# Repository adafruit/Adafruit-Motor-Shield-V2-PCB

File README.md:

## Adafruit Motor Shield V2 PCB

<a href="http://www.adafruit.com/products/1438"><br/>
Click here to purchase one from the Adafruit shop</a>

PCB files for Adafruit Motor Shield V2. 
- http://www.adafruit.com/products/1438

### DESCRIPTION
The original Adafruit Motorshield kit is one of our most beloved kits, which is why we decided to make something even better. We have upgraded the shield kit to make the bestest, easiest way to drive DC and Stepper motors. This shield will make quick work of your next robotics project! We kept the ability to drive up to 4 DC motors or 2 stepper motors, but added many improvements:

Instead of a L293D darlington driver, we now have the TB6612 MOSFET drivers with 1.2A per channel current capability (you can draw up to 3A peak for approx 20ms at a time). It also has much lower voltage drops across the motor so you get more torque out of your batteries, and there are built-in flyback diodes as well.

Instead of using a latch and the Arduino's PWM pins, we have a fully-dedicated PWM driver chip onboard. This chip handles all the motor and speed controls over I2C. Only two data pins (SDA & SCL in addition to the power pins GND & 5V) are required to drive the multiple motors, and since it's I2C you can also connect any other I2C devices or shields to the same pins. This also makes it drop-in compatible with any Arduino, such as the Uno, Due, Leonardo and Mega R3.

Completely stackable design: 5 address-select pins means up to 32 stackable shields: that's 64 steppers or 128 DC motors! What on earth could you do with that many steppers? I have no idea but if you come up with something send us a photo because that would be a pretty glorious project.

Lots of other little improvements such as a polarity protection FET on the power pins and a bit of prototyping area. And the shield is assembled and tested here at Adafruit so all you have to do is solder on straight or stacking headers and the terminal blocks.

### License

Adafruit invests time and resources providing this open source design, please support Adafruit and open-source hardware by purchasing products from [Adafruit.com](https://www.adafruit.com)!

Creative Commons Attribution, Share-Alike license, check license.txt for more information All text above must be included in any redistribution - 
See license.txt for more information.

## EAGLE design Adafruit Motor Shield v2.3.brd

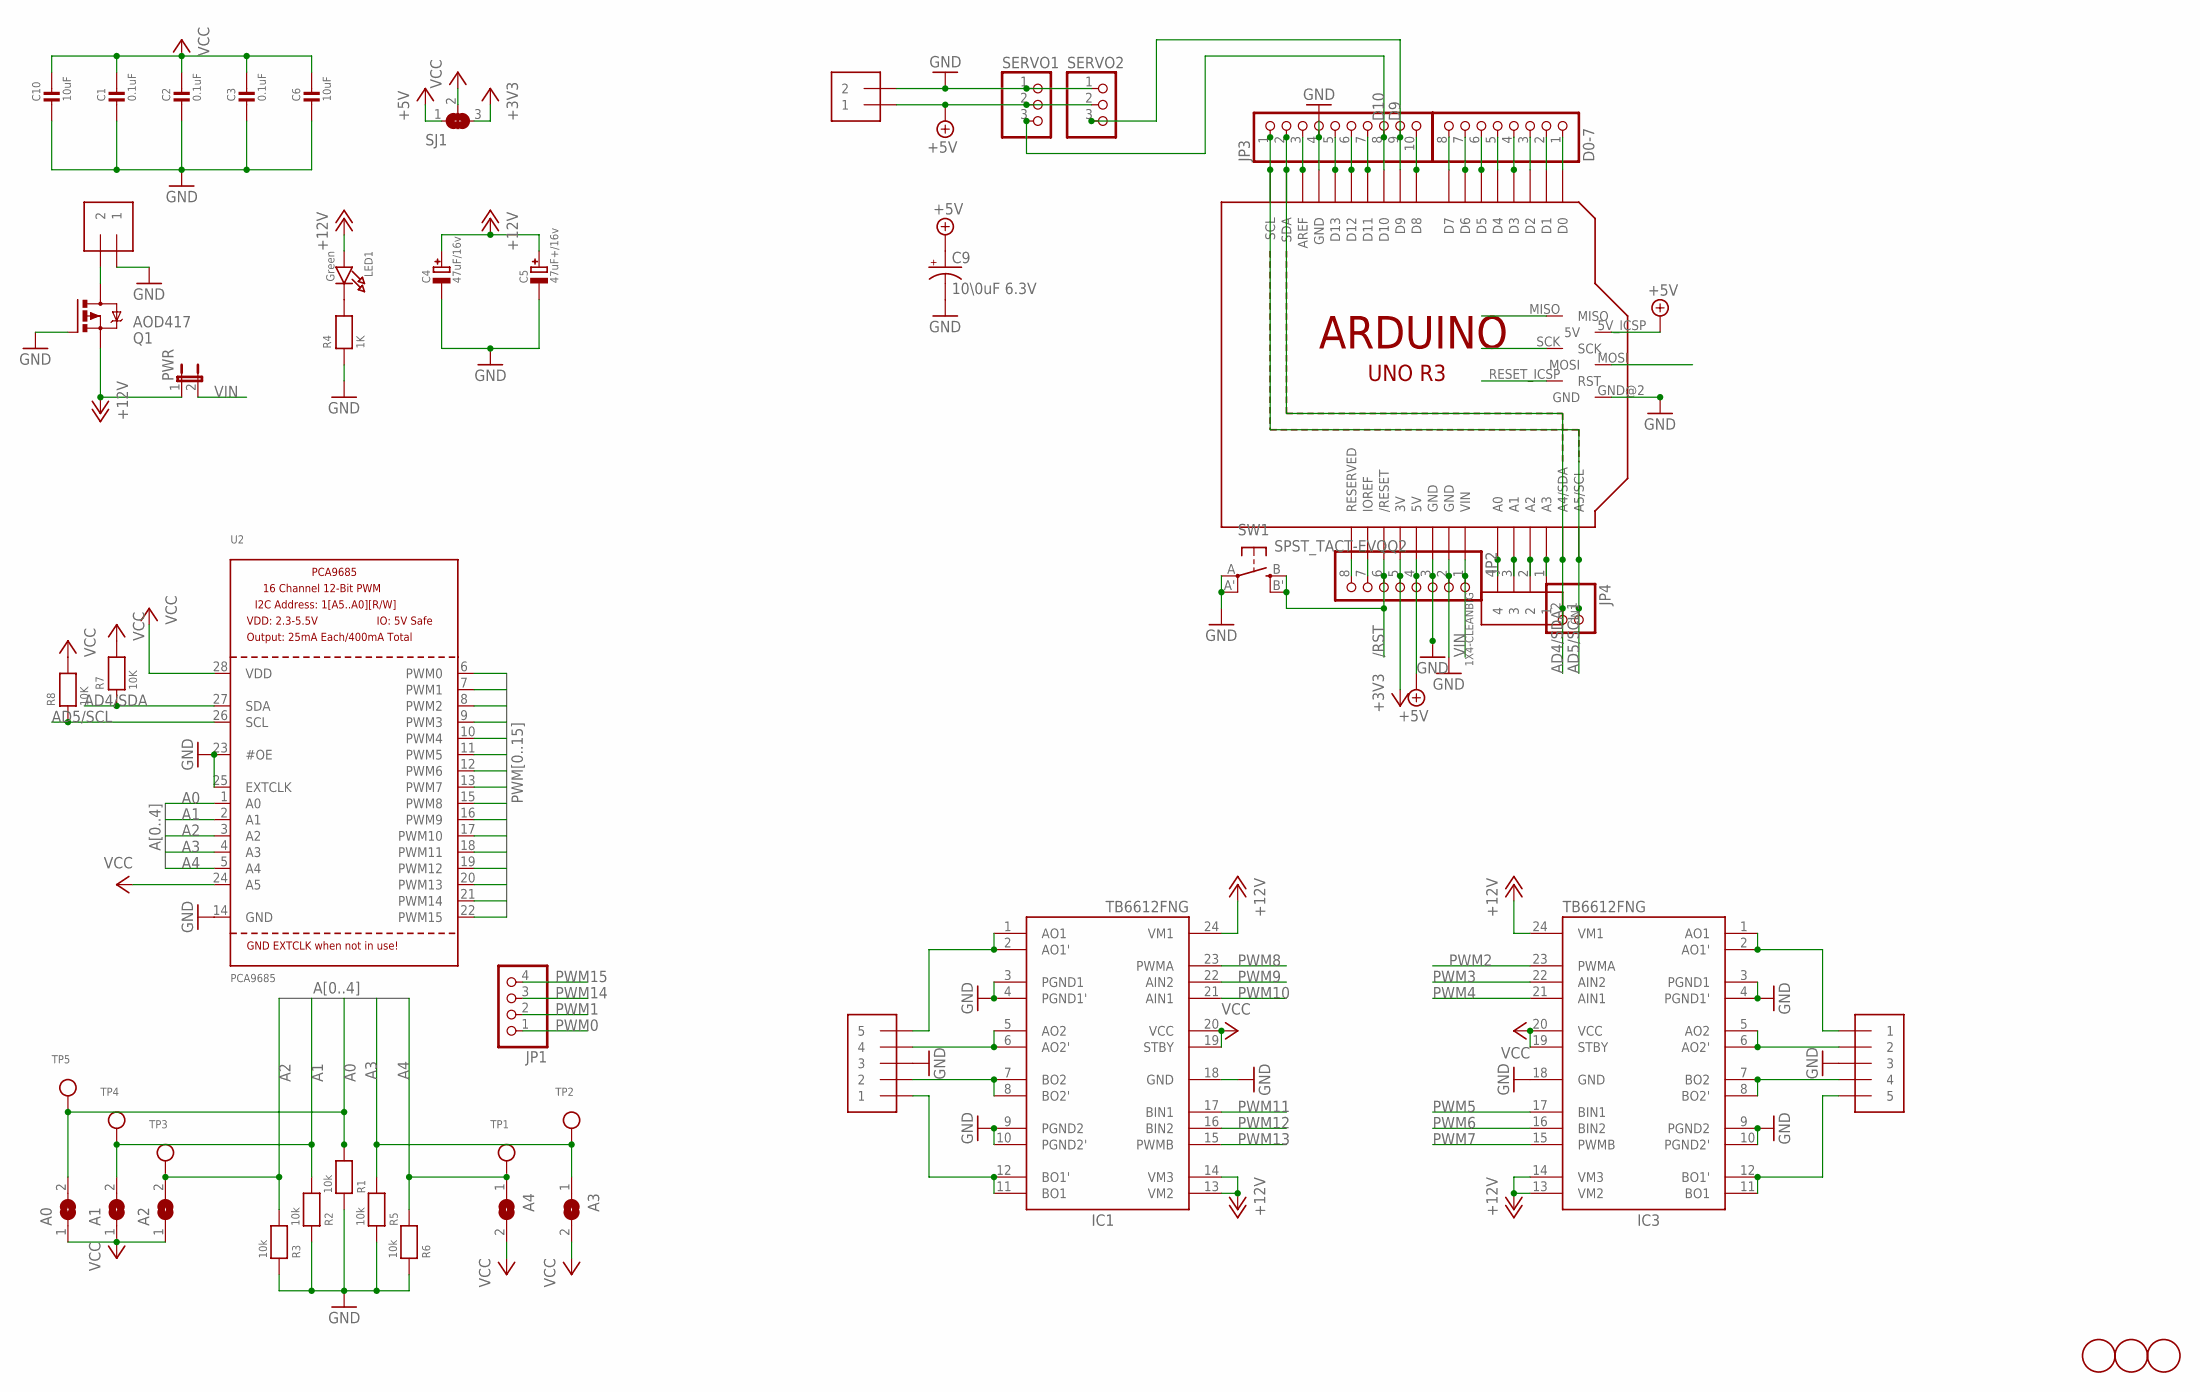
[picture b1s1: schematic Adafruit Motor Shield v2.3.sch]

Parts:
A0, A1, A2, A3, A4: SOLDERJUMPERREFLOW_NOPASTE; SOLDERJUMPER_REFLOW_NOPASTE
C1, C2, C3: 0.1uF; 0805-NO
C4: 47uF/16v; PANASONIC_C
C5: 47uF+/16v; PANASONIC_C
C6, C10: 10uF; 0805-NO
C9: 10\0uF 6.3V; PANASONIC_C
CN1: 1X4-CLEANBIG; 1X04-CLEANBIG
D0-7: PINHD-1X8CLEANBIG; 1X08-CLEANBIG
IC1, IC3: TB6612FNG; SSOP24
J1, J2: 1X5; 1X05-3.5MM
JP1: HEADER-1X476MIL; 1X04_ROUND_76
JP2: PINHD-1X8CLEANBIG; 1X08-CLEANBIG
JP3: HEADER-1X1070MIL; 1X10_ROUND70
JP4: HEADER-1X2ROUND; 1X02_ROUND
LED1: Green; CHIPLED_0805_NOOUTLINE
MPOWER: 1X2-3.5MM
PWR: JP1E; JP1
Q1: AOD417; D-PAK_TO252AA
R1, R2, R3, R5, R6: 10k; 0805-NO
R4: 1K; 0805-NO
R7, R8: 10K; 0805-NO
SERPWR: 1X2-3.5MM
SERVO1, SERVO2: PINHD-1X3; 1X03
SJ1: SOLDERJUMPER_2WAY; SOLDERJUMPER_2WAY_OPEN_NOPASTE
SW1: SPST_TACT-EVQQ2; EVQ-Q2
TP1, TP2, TP3, TP4, TP5: TESTPOINTROUND2MM; TESTPOINT_ROUND_2MM
U2: PCA9685; TSSOP28
U$1: ARDUINO_R3_ICSP; ARDUINOR3_ICSP
U$2, U$3, U$4: FIDUCIAL; FIDUCIAL_1MM

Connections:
+3V3: JP2.5, SJ1.3, U$1.3V
+5V: C9.+, JP2.4, SERPWR.1, SERVO1.2, SERVO2.2, SJ1.1, U$1.5V, U$1.5V_ICSP (5V)
+12V: C4.+, C5.+, IC1.13 (VM2), IC1.14 (VM3), IC1.24 (VM1), IC3.13 (VM2), IC3.14 (VM3), IC3.24 (VM1), LED1.A, PWR.1, Q1.3 (S)
/RST: JP2.6, SW1.B (S), SW1.B' (S1), U$1.RESET (/RESET), U$1.RESET_ICSP (RST)
A0: A0.2, R1.2, TP5.P$1, U2.1 (A0)
A1: A1.2, R2.2, TP4.P$1, U2.2 (A1)
A2: A2.2, R3.2, TP3.P$1, U2.3 (A2)
A3: A3.1, R5.2, TP2.P$1, U2.4 (A3)
A4: A4.1, R6.2, TP1.P$1, U2.5 (A4)
AD0: CN1.4, U$1.A0
AD1: CN1.3, U$1.A1
AD2: CN1.2, U$1.A2
AD3: CN1.1, U$1.A3
AD4/SDA: JP3.2, JP4.2, R7.1, U2.27 (SDA), U$1.A4 (A4/SDA), U$1.SDA
AD5/SCL: JP3.1, JP4.1, R8.1, U2.26 (SCL), U$1.A5 (A5/SCL), U$1.SCL
AREF: JP3.3, U$1.AREF
D0: D0-7.1, U$1.D0
D1: D0-7.2, U$1.D1
D2: D0-7.3, U$1.D2
D3: D0-7.4, U$1.D3
D4: D0-7.5, U$1.D4
D5: D0-7.6, U$1.D5
D6: D0-7.7, U$1.D6
D7: D0-7.8, U$1.D7
D8: JP3.10, U$1.D8
D9: JP3.9, SERVO2.3, U$1.D9
D10: JP3.8, SERVO1.3, U$1.D10
D11: JP3.7, U$1.D11
D12: JP3.6, U$1.D12
D13: JP3.5, U$1.D13
GND: C1.2, C2.2, C3.2, C4.-, C5.-, C6.2, C9.-, C10.2, IC1.3 (PGND1), IC1.4 (PGND1'), IC1.9 (PGND2), IC1.10 (PGND2'), IC1.18 (GND), IC3.3 (PGND1), IC3.4 (PGND1'), IC3.9 (PGND2), IC3.10 (PGND2'), IC3.18 (GND), J1.3, J2.3, JP2.2, JP2.3, JP3.4, MPOWER.1, Q1.1 (G), R1.1, R2.1, R3.1, R4.1, R5.1, R6.1, SERPWR.2, SERVO1.1, SERVO2.1, SW1.A, SW1.A' (P1), U2.14 (GND), U2.23 (#OE), U2.25 (EXTCLK), U$1.GND, U$1.GND@1 (GND), U$1.GND@2 (GND), U$1.GND@3 (GND)
IOREF: JP2.7, U$1.IOREF
M1A: IC1.1 (AO1), IC1.2 (AO1'), J1.5
M1B: IC1.5 (AO2), IC1.6 (AO2'), J1.4
M2A: IC1.11 (BO1), IC1.12 (BO1'), J1.1
M2B: IC1.7 (BO2), IC1.8 (BO2'), J1.2
M3A: IC3.1 (AO1), IC3.2 (AO1'), J2.1
M3B: IC3.5 (AO2), IC3.6 (AO2'), J2.2
M4A: IC3.11 (BO1), IC3.12 (BO1'), J2.5
M4B: IC3.7 (BO2), IC3.8 (BO2'), J2.4
MISO: U$1.MISO
MOSI: U$1.MOSI
unnamed: JP2.8, U$1.RESERVED
unnamed: LED1.C, R4.2
PWM0: JP1.1, U2.6 (PWM0)
PWM1: JP1.2, U2.7 (PWM1)
PWM2: IC3.23 (PWMA), U2.8 (PWM2)
PWM3: IC3.22 (AIN2), U2.9 (PWM3)
PWM4: IC3.21 (AIN1), U2.10 (PWM4)
PWM5: IC3.17 (BIN1), U2.11 (PWM5)
PWM6: IC3.16 (BIN2), U2.12 (PWM6)
PWM7: IC3.15 (PWMB), U2.13 (PWM7)
PWM8: IC1.23 (PWMA), U2.15 (PWM8)
PWM9: IC1.22 (AIN2), U2.16 (PWM9)
PWM10: IC1.21 (AIN1), U2.17 (PWM10)
PWM11: IC1.17 (BIN1), U2.18 (PWM11)
PWM12: IC1.16 (BIN2), U2.19 (PWM12)
PWM13: IC1.15 (PWMB), U2.20 (PWM13)
PWM14: JP1.3, U2.21 (PWM14)
PWM15: JP1.4, U2.22 (PWM15)
SCK: U$1.SCK
VCC: A0.1, A1.1, A2.1, A3.2, A4.2, C1.1, C2.1, C3.1, C6.1, C10.1, IC1.19 (STBY), IC1.20 (VCC), IC3.19 (STBY), IC3.20 (VCC), R7.2, R8.2, SJ1.2, U2.24 (A5), U2.28 (VDD)
VIN: JP2.1, PWR.2, U$1.VIN
VMOTOR: MPOWER.2, Q1.4 (D)

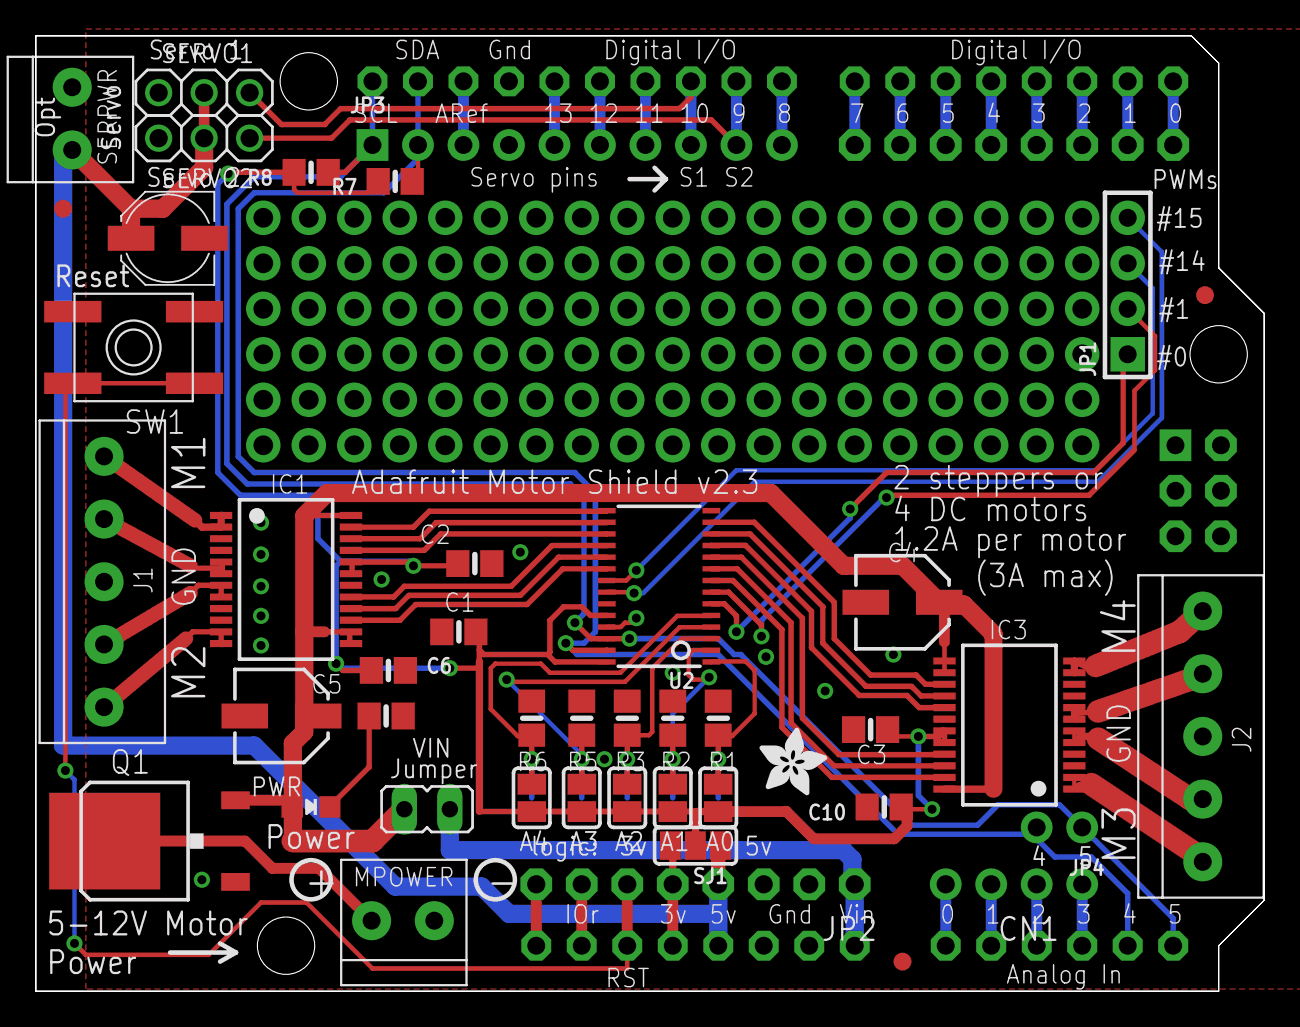
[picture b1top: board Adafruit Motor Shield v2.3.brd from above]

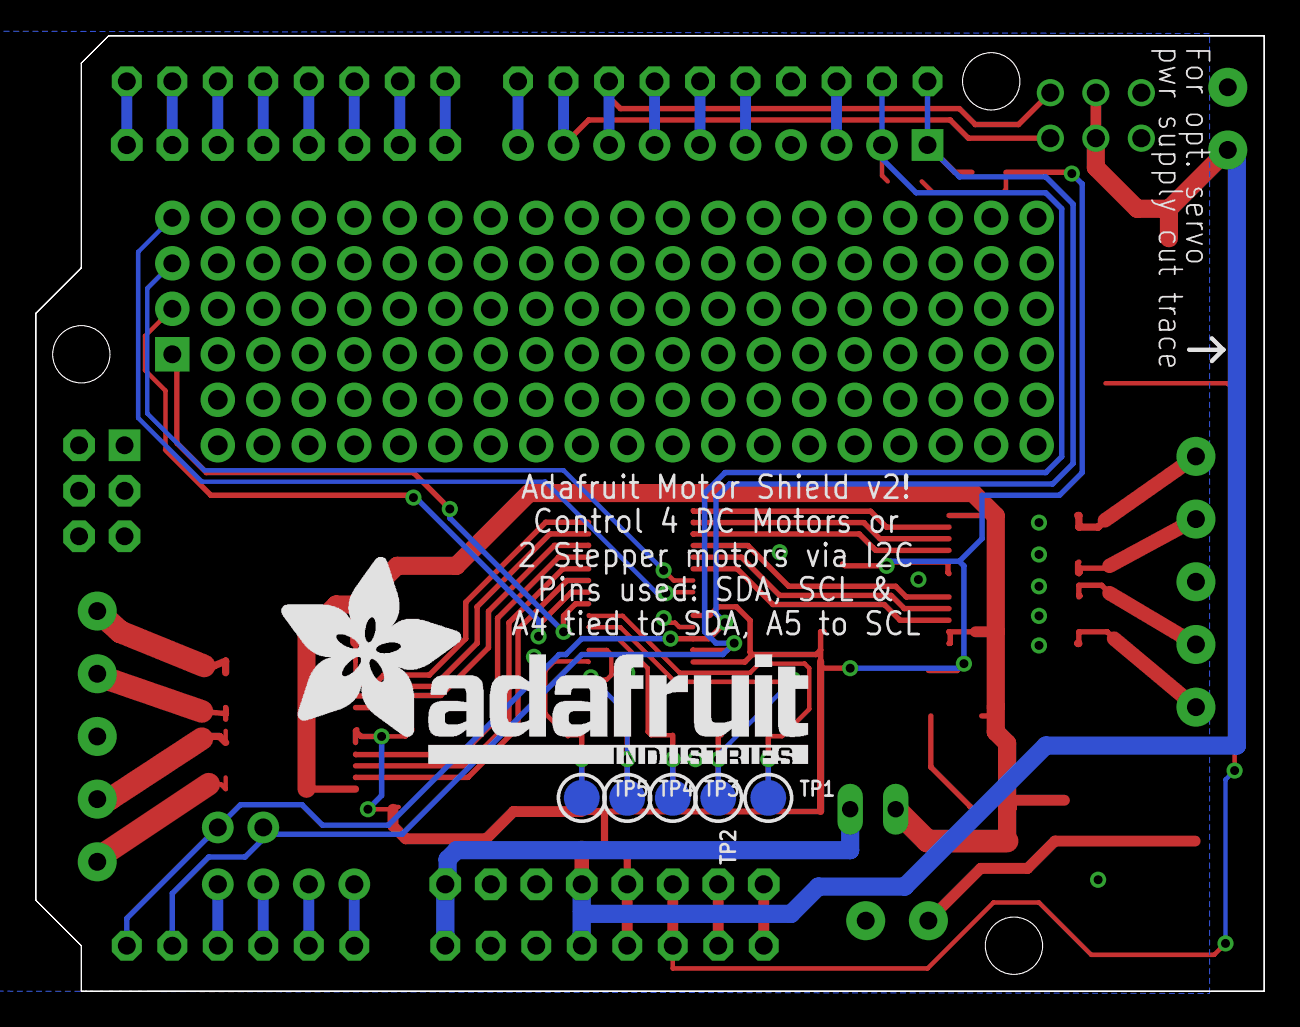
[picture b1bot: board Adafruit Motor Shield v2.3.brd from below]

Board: 2 copper layers, 68.6 x 53.3 mm, 52 parts (6 on the bottom side), 61 nets.

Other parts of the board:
U$5: ADAFRUIT_TEXT_30MM
U$6: ADAFRUIT_3.5MM

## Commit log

2014-06-02 init!
2016-10-26 added very latest

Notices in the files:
parts and their libraries:
microbuilder: This work is placed in the public domain, and may be freely used for commercial and non-commercial work with the following conditions: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
